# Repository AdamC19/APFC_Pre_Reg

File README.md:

# APFC Pre-Regulator
Hardware and Software for my Active Power Factor Correction Pre-Regulator

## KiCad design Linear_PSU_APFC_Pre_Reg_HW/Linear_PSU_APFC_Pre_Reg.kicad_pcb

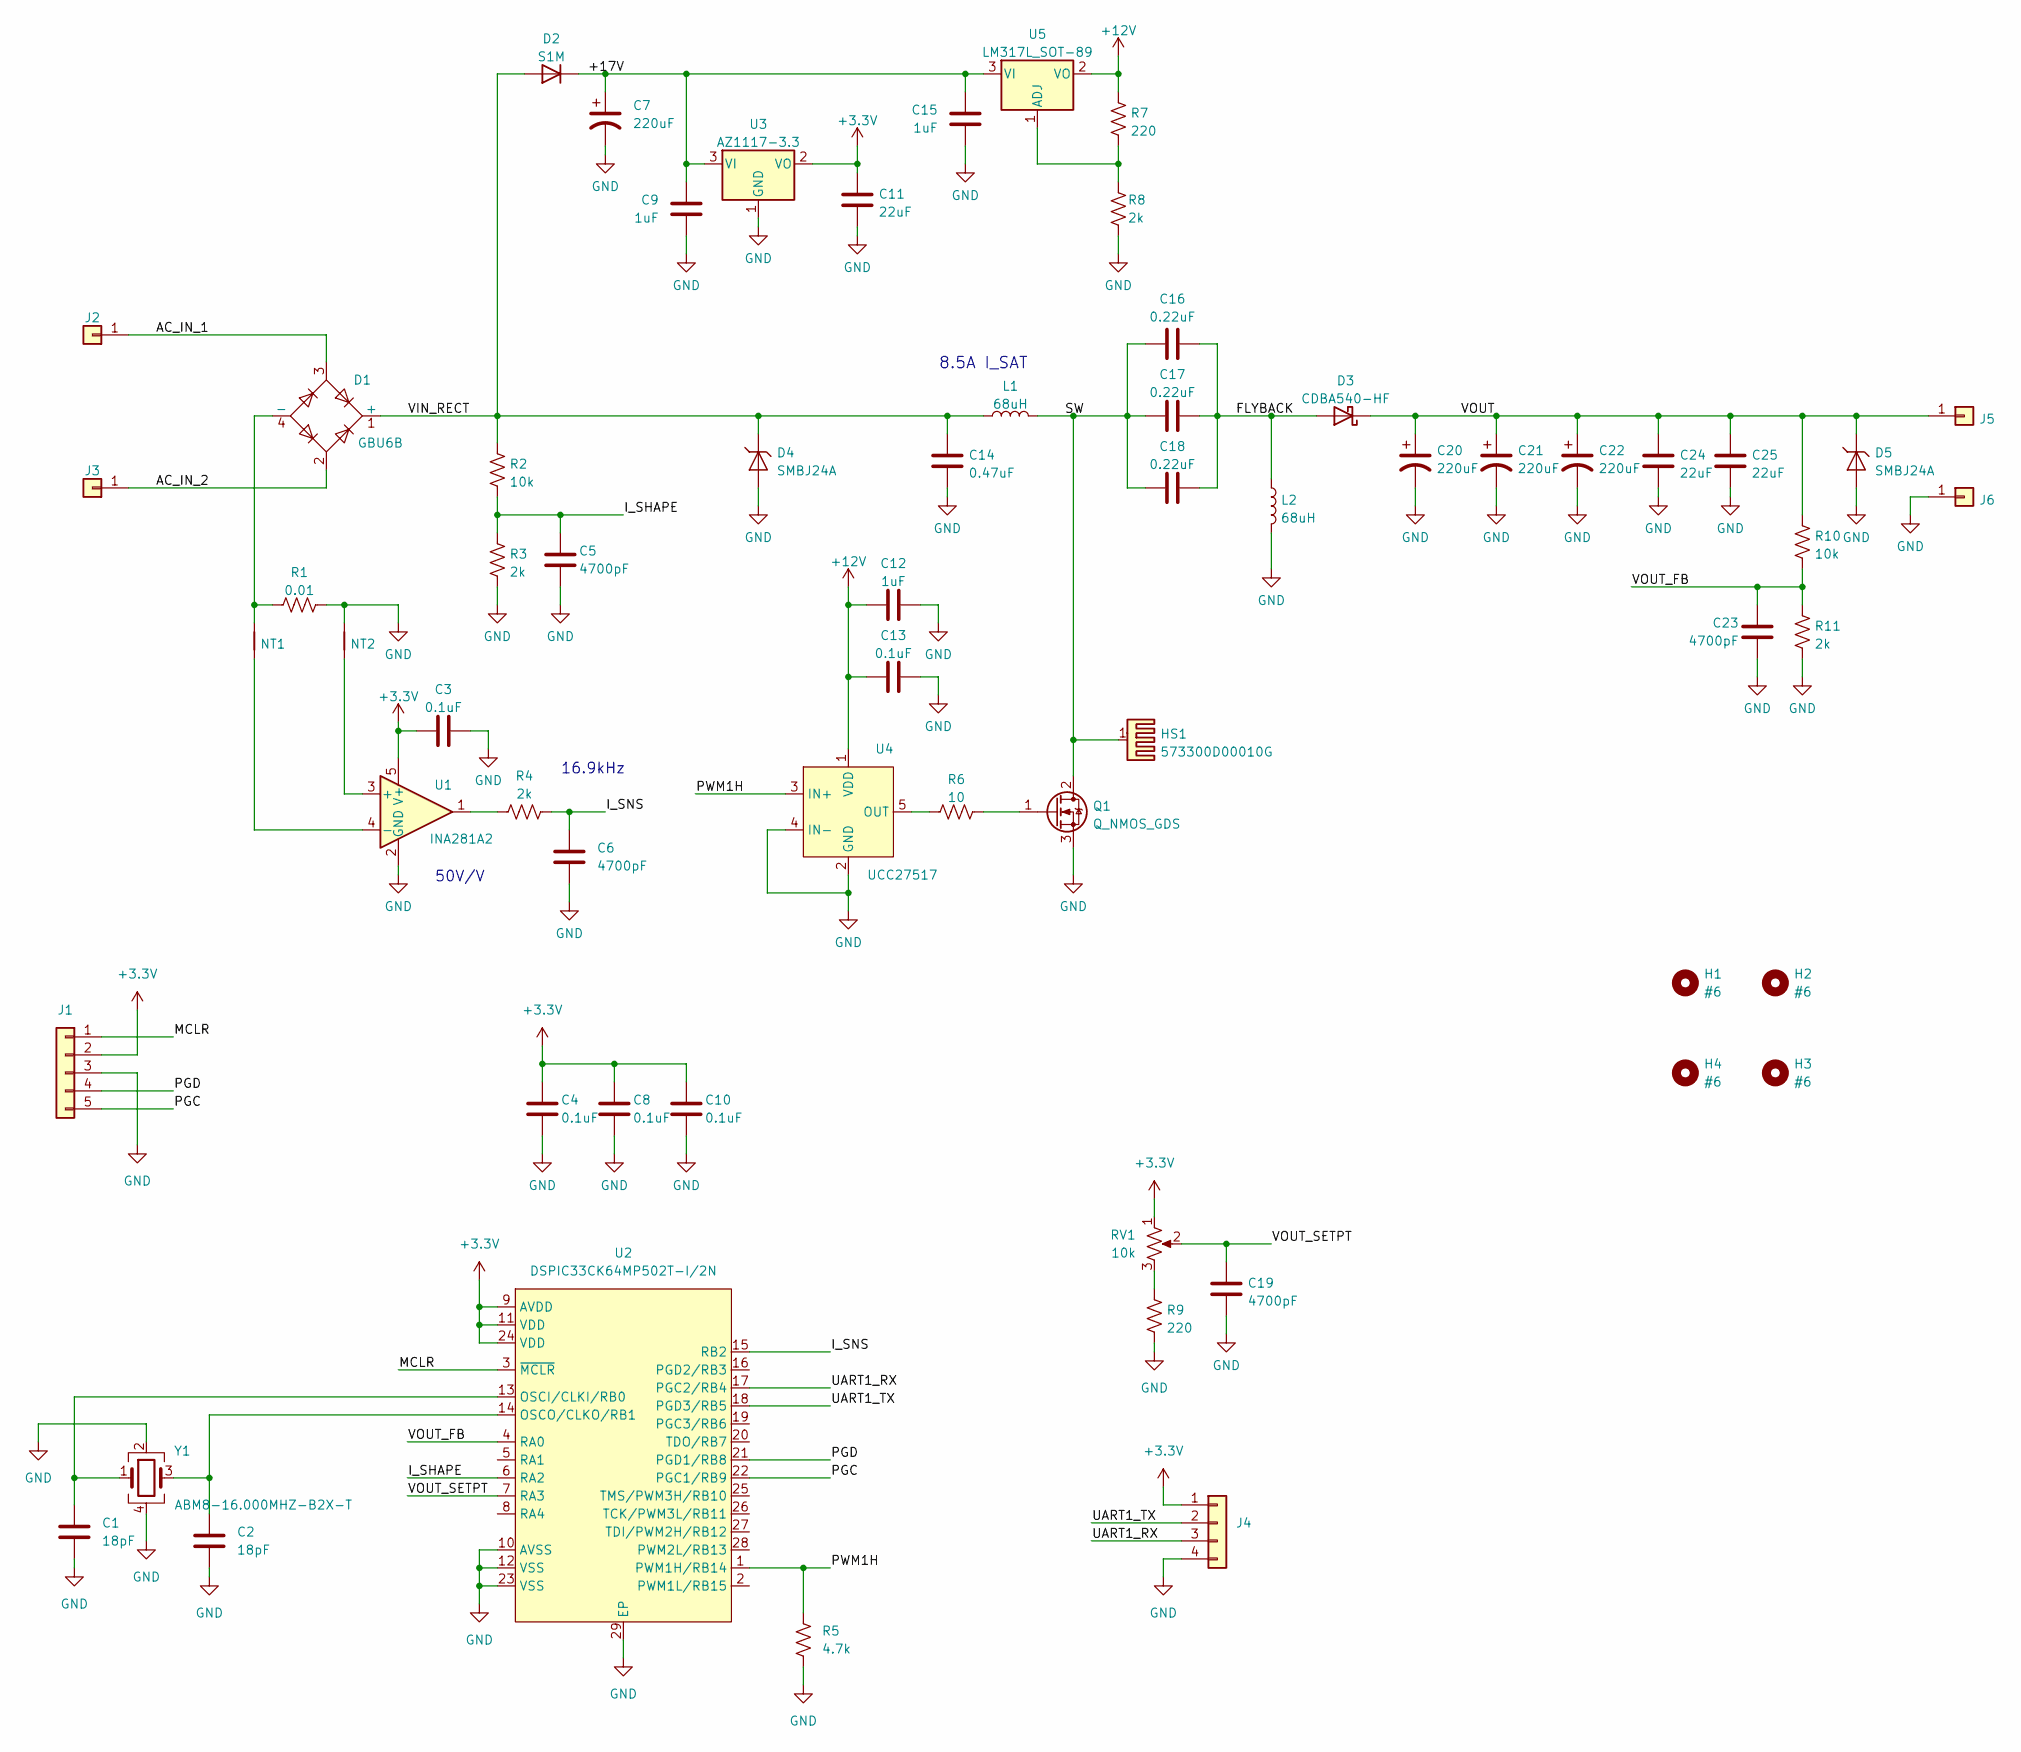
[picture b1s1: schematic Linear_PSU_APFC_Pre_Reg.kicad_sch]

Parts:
C1, C2: 18pF; C_0603_1608Metric
C3, C4, C8, C10, C13: 0.1uF; C_0603_1608Metric
C5, C6, C19, C23: 4700pF; C_0603_1608Metric
C7: 220uF; CP_Elec_10x10.5
C9, C12, C15: 1uF; C_0805_2012Metric
C11, C24, C25: 22uF; C_1210_3225Metric
C14: 0.47uF; C_0805_2012Metric
C16, C17, C18: 0.22uF; C_0805_2012Metric
C20, C21, C22: 220uF; CP_Radial_D8.0mm_P3.50mm
D1: GBU6B; Diode_Bridge_Vishay_GBU
D2: S1M; D_SMA
D3: CDBA540-HF; D_SMA; MFG_PN CDBA540-HF
D4, D5: SMBJ24A; D_SMB
H1, H2, H3, H4: #6; MountingHole_3.7mm
HS1: 573300D00010G; Heatsink_AAVID_573300D00010G_TO-263
J1: Conn_01x05; PinHeader_1x05_P2.54mm_Vertical
J2, J3, J5, J6: Conn_01x01; TE_Connectivity_63824-1
J4: Conn_01x04; PinHeader_1x04_P2.54mm_Vertical
L1, L2: 68uH; L_Bourns_SRP1770TA_16.9x16.9mm; MFG_PN SRP1770TA-680M
NT1, NT2: NetTie_2; NetTie-2_SMD_Pad0.25mm
Q1: Q_NMOS_GDS; TO-263-2
R1: 0.01; R_1206_3216Metric
R2, R10: 10k; R_0603_1608Metric
R3, R4, R8, R11: 2k; R_0603_1608Metric
R5: 4.7k; R_0603_1608Metric
R6: 10; R_0805_2012Metric
R7, R9: 220; R_0603_1608Metric
RV1: 10k; Potentiometer_Bourns_3386P_Vertical
U1: INA281A2; SOT-23-5
U2: DSPIC33CK64MP502T-I/2N; UQFN-28-1EP_6x6mm_P0.65mm_EP4.65x4.65mm; MFG_PN DSPIC33CK64MP502T-I/2N
U3: AZ1117-3.3; SOT-89-3
U4: UCC27517; SOT-23-5; MFG_PN UCC27517DBVR
U5: LM317L_SOT-89; SOT-89-3
Y1: ABM8-16.000MHZ-B2X-T; Crystal_SMD_EuroQuartz_MT-4Pin_3.2x2.5mm

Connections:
+3.3V: C3.1, C4.2, C8.2, C10.2, C11.1, J1.2, J4.1, RV1.1, U1.5 (V+), U2.9 (AVDD), U2.11 (VDD), U2.24 (VDD), U3.2 (VO)
+12V: C12.1, C13.1, R7.1, U4.1 (VDD), U5.2 (VO)
/+17V: C7.1, C9.2, C15.2, D2.1 (K), U3.3 (VI), U5.3 (VI)
/AC_IN_1: D1.3, J2.1
/AC_IN_2: D1.2, J3.1
/FLYBACK: C16.1, C17.1, C18.1, D3.2 (A), L2.1
/I_SHAPE: C5.2, R2.2, R3.1, U2.6 (RA2)
/I_SNS: C6.2, R4.1, U2.15 (RB2)
/MCLR: J1.1, U2.3 (~MCLR)
/PGC: J1.5, U2.22 (PGC1/RB9)
/PGD: J1.4, U2.21 (PGD1/RB8)
/PWM1H: R5.1, U2.1 (PWM1H/RB14), U4.3 (IN+)
/SW: C16.2, C17.2, C18.2, HS1.1, L1.2, Q1.2 (D)
/UART1_RX: J4.3, U2.17 (PGC2/RB4)
/UART1_TX: J4.2, U2.18 (PGD3/RB5)
/VIN_RECT: C14.2, D1.1 (+), D2.2 (A), D4.1 (K), L1.1, R2.1
/VOUT: C20.1, C21.1, C22.1, C24.1, C25.1, D3.1 (K), D5.1 (K), J5.1, R10.1
/VOUT_FB: C23.2, R10.2, R11.1, U2.4 (RA0)
/VOUT_SETPT: C19.2, RV1.2, U2.7 (RA3)
GND: C1.2, C2.2, C3.2, C4.1, C5.1, C6.1, C7.2, C8.1, C9.1, C10.1, C11.2, C12.2, C13.2, C14.1, C15.1, C19.1, C20.2, C21.2, C22.2, C23.1, C24.2, C25.2, D4.2 (A), D5.2 (A), J1.3, J4.4, J6.1, L2.2, NT2.2, Q1.3 (S), R1.2, R3.2, R5.2, R8.2, R9.2, R11.2, U1.2 (GND), U2.10 (AVSS), U2.12 (VSS), U2.23 (VSS), U2.29 (EP), U3.1 (GND), U4.2 (GND), U4.4 (IN-), Y1.2, Y1.4
unnamed: C1.1, U2.13 (OSCI/CLKI/RB0), Y1.1
unnamed: C2.1, U2.14 (OSCO/CLKO/RB1), Y1.3
unnamed: D1.4 (-), NT1.2, R1.1
unnamed: NT1.1, U1.4 (-)
unnamed: NT2.1, U1.3 (+)
unnamed: Q1.1 (G), R6.1
unnamed: R4.2, U1.1
unnamed: R6.2, U4.5 (OUT)
unnamed: R7.2, R8.1, U5.1 (ADJ)
unnamed: R9.1, RV1.3

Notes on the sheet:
16.9kHz
50V/V
8.5A I_SAT

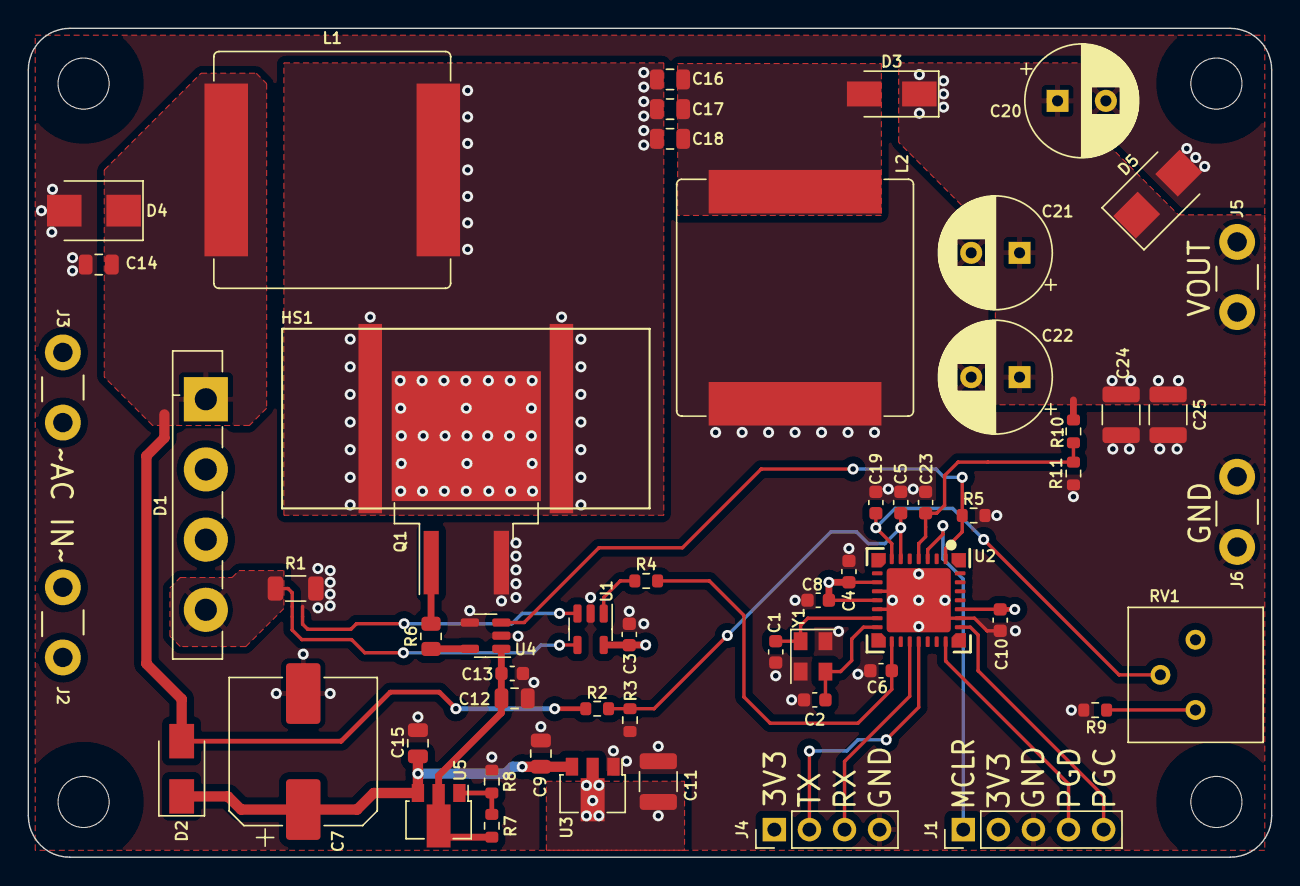
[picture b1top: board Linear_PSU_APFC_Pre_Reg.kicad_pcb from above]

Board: 4 copper layers, 90.0 x 60.0 mm, 64 parts (0 on the bottom side), 30 nets.

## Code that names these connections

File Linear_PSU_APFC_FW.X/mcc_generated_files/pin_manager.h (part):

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*/
/**
  @Summary
    Sets the GPIO pin, RA0, high using LATA0.

  @Description
    Sets the GPIO pin, RA0, high using LATA0.

  @Preconditions
    The RA0 must be set to an output.
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#define VOUT_FB_SetHigh()          (_LATA0 = 1)
/**
  @Summary
    Sets the GPIO pin, RA0, low using LATA0.

  @Description
    Sets the GPIO pin, RA0, low using LATA0.

  @Preconditions
    The RA0 must be set to an output.
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#define VOUT_FB_SetLow()           (_LATA0 = 0)
/**
  @Summary
    Toggles the GPIO pin, RA0, using LATA0.

  @Description
    Toggles the GPIO pin, RA0, using LATA0.

  @Preconditions
    The RA0 must be set to an output.
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#define VOUT_FB_Toggle()           (_LATA0 ^= 1)
/**
  @Summary
    Reads the value of the GPIO pin, RA0.

  @Description
    Reads the value of the GPIO pin, RA0.

  @Preconditions
    None.
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    </code>

*/
#define VOUT_FB_GetValue()         _RA0
/**
  @Summary
    Configures the GPIO pin, RA0, as an input.

  @Description
    Configures the GPIO pin, RA0, as an input.

  @Preconditions
    None.
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#define VOUT_FB_SetDigitalInput()  (_TRISA0 = 1)
/**
  @Summary
    Configures the GPIO pin, RA0, as an output.

  @Description
    Configures the GPIO pin, RA0, as an output.

  @Preconditions
    None.
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#define VOUT_FB_SetDigitalOutput() (_TRISA0 = 0)
/**
  @Summary
    Sets the GPIO pin, RA2, high using LATA2.

  @Description
    Sets the GPIO pin, RA2, high using LATA2.

  @Preconditions
    The RA2 must be set to an output.
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#define I_SHAPE_SetHigh()          (_LATA2 = 1)
/**
  @Summary
    Sets the GPIO pin, RA2, low using LATA2.

  @Description
    Sets the GPIO pin, RA2, low using LATA2.

  @Preconditions
    The RA2 must be set to an output.
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#define I_SHAPE_SetLow()           (_LATA2 = 0)
/**
  @Summary
    Toggles the GPIO pin, RA2, using LATA2.

  @Description
    Toggles the GPIO pin, RA2, using LATA2.

  @Preconditions
    The RA2 must be set to an output.
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#define I_SHAPE_Toggle()           (_LATA2 ^= 1)
/**
  @Summary
    Reads the value of the GPIO pin, RA2.

  @Description
    Reads the value of the GPIO pin, RA2.

  @Preconditions
    None.
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    </code>

*/
#define I_SHAPE_GetValue()         _RA2
/**
  @Summary
    Configures the GPIO pin, RA2, as an input.

  @Description
    Configures the GPIO pin, RA2, as an input.

  @Preconditions
    None.
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#define I_SHAPE_SetDigitalInput()  (_TRISA2 = 1)
/**
  @Summary
    Configures the GPIO pin, RA2, as an output.

  @Description
    Configures the GPIO pin, RA2, as an output.

  @Preconditions
    None.
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#define I_SHAPE_SetDigitalOutput() (_TRISA2 = 0)
/**
  @Summary
    Sets the GPIO pin, RA3, high using LATA3.

  @Description
    Sets the GPIO pin, RA3, high using LATA3.

  @Preconditions
    The RA3 must be set to an output.
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#define VOUT_SETPT_SetHigh()          (_LATA3 = 1)
/**
  @Summary
    Sets the GPIO pin, RA3, low using LATA3.

  @Description
    Sets the GPIO pin, RA3, low using LATA3.

  @Preconditions
    The RA3 must be set to an output.
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#define VOUT_SETPT_SetLow()           (_LATA3 = 0)
/**
  @Summary
    Toggles the GPIO pin, RA3, using LATA3.

  @Description
    Toggles the GPIO pin, RA3, using LATA3.

  @Preconditions
    The RA3 must be set to an output.
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#define VOUT_SETPT_Toggle()           (_LATA3 ^= 1)
/**
  @Summary
    Reads the value of the GPIO pin, RA3.

  @Description
    Reads the value of the GPIO pin, RA3.

  @Preconditions
    None.
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    </code>

*/
#define VOUT_SETPT_GetValue()         _RA3
/**
  @Summary
    Configures the GPIO pin, RA3, as an input.

  @Description
    Configures the GPIO pin, RA3, as an input.

  @Preconditions
    None.
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#define VOUT_SETPT_SetDigitalInput()  (_TRISA3 = 1)
/**
  @Summary
    Configures the GPIO pin, RA3, as an output.

  @Description
    Configures the GPIO pin, RA3, as an output.

  @Preconditions
    None.
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#define VOUT_SETPT_SetDigitalOutput() (_TRISA3 = 0)
/**
  @Summary
    Sets the GPIO pin, RB2, high using LATB2.

  @Description
    Sets the GPIO pin, RB2, high using LATB2.

  @Preconditions
    The RB2 must be set to an output.
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#define I_SNS_SetHigh()          (_LATB2 = 1)
/**
  @Summary
    Sets the GPIO pin, RB2, low using LATB2.

  @Description
    Sets the GPIO pin, RB2, low using LATB2.

  @Preconditions
    The RB2 must be set to an output.
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#define I_SNS_SetLow()           (_LATB2 = 0)
/**
  @Summary
    Toggles the GPIO pin, RB2, using LATB2.

  @Description
    Toggles the GPIO pin, RB2, using LATB2.

  @Preconditions
    The RB2 must be set to an output.
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#define I_SNS_Toggle()           (_LATB2 ^= 1)
/**
  @Summary
    Reads the value of the GPIO pin, RB2.

  @Description
    Reads the value of the GPIO pin, RB2.

  @Preconditions
    None.
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    </code>

*/
#define I_SNS_GetValue()         _RB2
/**
  @Summary
    Configures the GPIO pin, RB2, as an input.

  @Description
    Configures the GPIO pin, RB2, as an input.

  @Preconditions
    None.
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#define I_SNS_SetDigitalInput()  (_TRISB2 = 1)
/**
  @Summary
    Configures the GPIO pin, RB2, as an output.

  @Description
    Configures the GPIO pin, RB2, as an output.

  @Preconditions
    None.
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
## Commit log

2022-10-12 Initial commit of hardware files
2022-10-12 Initial commit of software

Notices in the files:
Linear_PSU_APFC_FW.X/mcc_generated_files/pin_manager.h:
(c) 2020 Microchip Technology Inc. and its subsidiaries. You may use this
Linear_PSU_APFC_Pre_Reg_HW/Linear_PSU_APFC_Pre_Reg.kicad_pcb:
(C) 2022 ADAM CORDINGLEY
